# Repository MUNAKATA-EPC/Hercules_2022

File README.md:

# Hercules_2022

ヘラクレス2022シーズンのソースコード、基板データを公開しています。

詳しくはWikiを参照。

## 運用方針

- 大きな変更をするときはブランチを絶対に別途作成しましょう
- 小さな変更(スペルミスやコメント修正程度)ならどんどんmainブランチに突っ込んでもまあ構わないでしょう
- 余裕があったら変更した内容をコメントしてくれると助かります

## コードに関して

- 各プロジェクトフォルダの命名規則は「hogehoge(プロジェクト名)-teensy40(開発環境名)」となっていますが、一部試験用に作ったものに関しては、この命名規則が守られておりません...ごめんなさい。
- プロジェクトフォルダ内の「src」フォルダ内にmain.cpp(一部プロジェクトは名称が異なります)、「lib」フォルダ内に各種ライブラリ、「include」フォルダ内にサブプログラムが入っています。
- 一部PlatformIOからダウンロードしているライブラリが含まれているため、基本は「VSCode + PlatformIO」の組み合わせでご覧ください。

## 回路に関して

- 使用する設計ソフトにKiCad5と6が混在しています。
- ライブラリについてはLibraryフォルダを相対パスで参照しています。
- 発注は主にJLCPCBを使用します。

## 開発環境に関して

- VSCodeの拡張機能のPlatformIOを使用しTeensy 4.0とSeeeduino XIAOに書き込んでいます。
- 弊チームにはMacユーザーがいないため、Windows環境での開発を想定しております。Macをお使いの皆様、何か問題が生じても対応はできません。予めご了承ください。

## ライセンスに関して

- すべてのコード、基板データに関するライセンスはMITにしていますが、ライブラリ等のライセンスはそのライブラリごとのライセンスに従ってください。

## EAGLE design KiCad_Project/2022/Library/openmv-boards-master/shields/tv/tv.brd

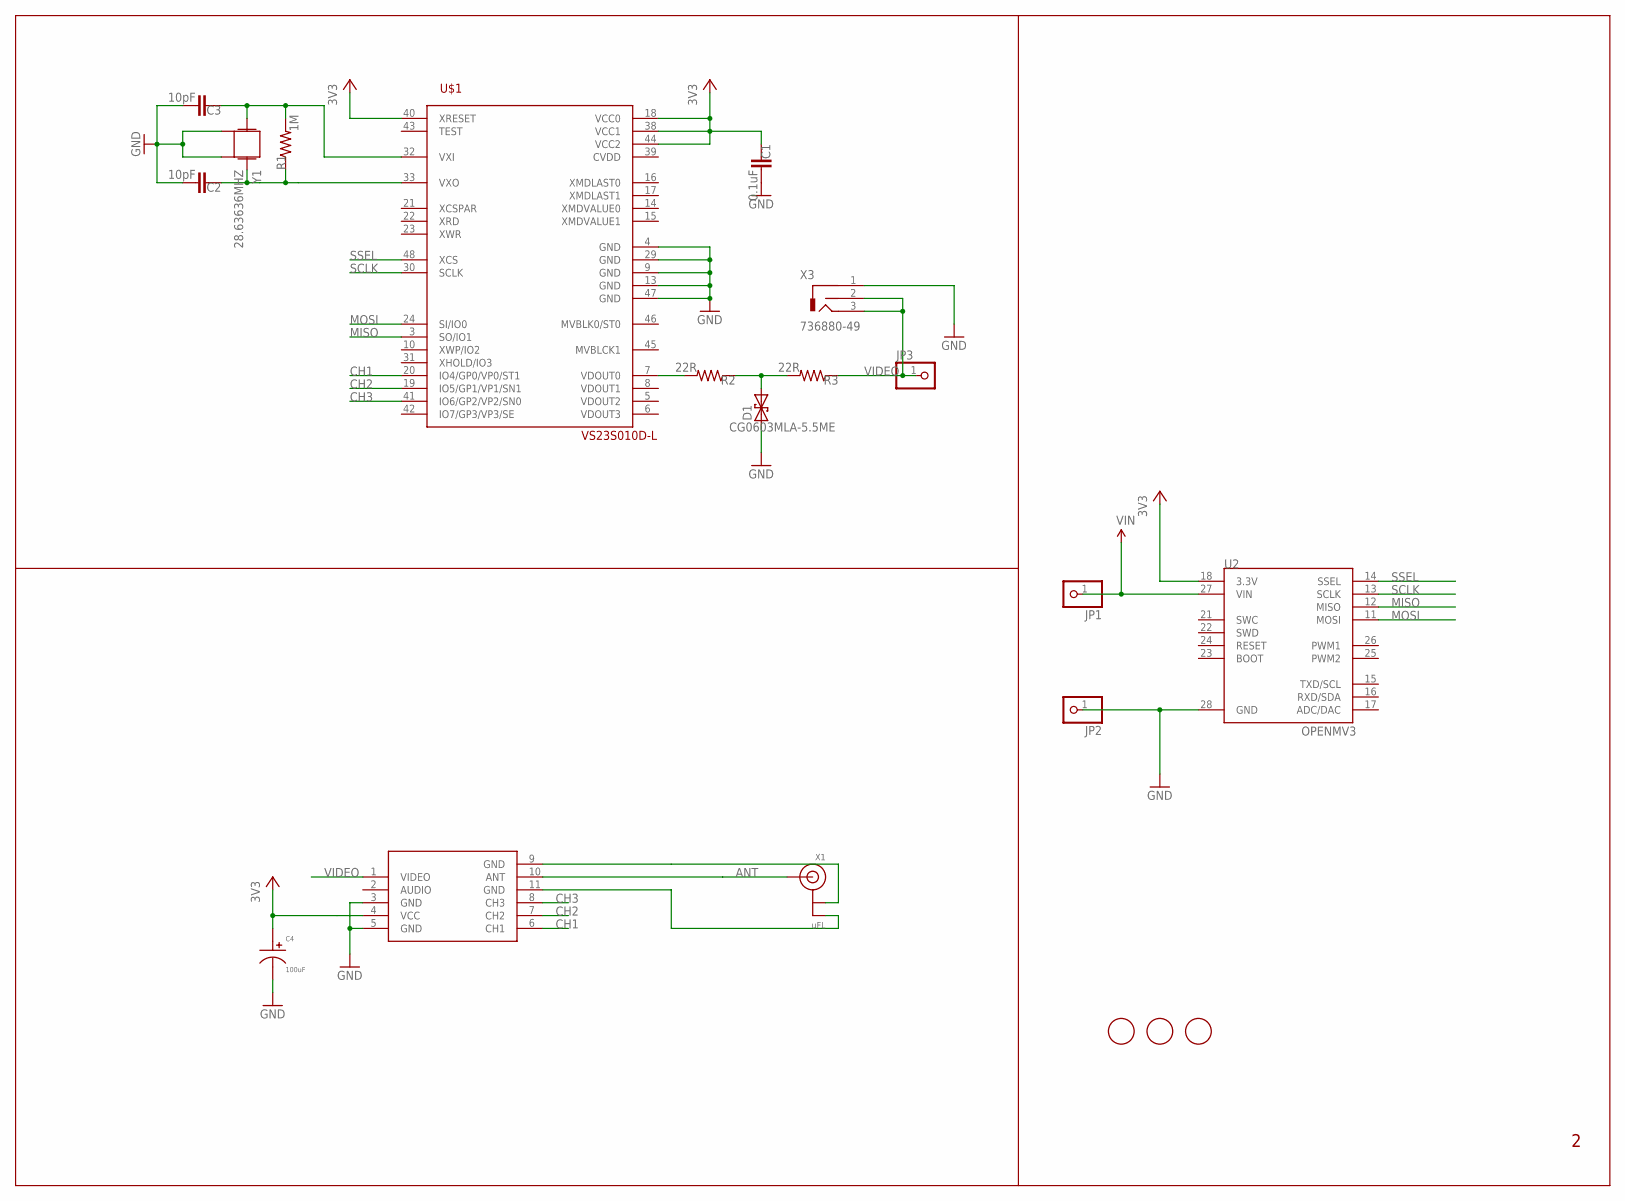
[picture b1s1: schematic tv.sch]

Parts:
C1: 0.1uF; 0603-CAP
C2, C3: 10pF; 0603-CAP
C4: 100uF; CP6.3MM
D1: CG0603MLA-5.5ME; C0603K
JP1, JP2, JP3: PINHD-1X1; 1X01
R1: 1M; 0603-RES
R2, R3: 22R; 0603-RES
U1: VS23S010D-L; LQFP48
U2: OPENMV3
U3: TX5813
U$1, U$2, U$4: FIDUCIAL; FIDUCIAL_1MM
X1: uFL; U.FL
X3: 736880-49
Y1: 28.63636MHZ; CRYSTAL-3.2X2.5-CTX851CT

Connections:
3V3: C1.1, C4.P$1, U1.18 (VCC0), U1.38 (VCC1), U1.40 (XRESET), U1.44 (VCC2), U2.18 (3.3V), U3.4 (VCC)
ANT: U3.10 (ANT), X1.3 (SIGNAL)
CH1: U1.20 (IO4/GP0/VP0/ST1), U3.6 (CH1)
CH2: U1.19 (IO5/GP1/VP1/SN1), U3.7 (CH2)
CH3: U1.41 (IO6/GP2/VP2/SN0), U3.8 (CH3)
GND: C1.2, C2.2, C3.2, C4.P$2, D1.1, JP2.1, U1.4 (GND), U1.9 (GND), U1.13 (GND), U1.29 (GND), U1.47 (GND), U2.28 (GND), U3.3 (GND), U3.5 (GND), X3.1 (GND), Y1.2, Y1.4
MISO: U1.3 (SO/IO1), U2.12 (MISO)
MOSI: U1.24 (SI/IO0), U2.11 (MOSI)
unnamed: D1.2, R2.1, R3.2
unnamed: R2.2, U1.7 (VDOUT0)
unnamed: U3.11 (GND), X1.2 (GND)
unnamed: U3.9 (GND), X1.1 (GND)
unnamed: C3.1, R1.2, U1.32 (VXI), Y1.3 (2)
unnamed: C2.1, R1.1, U1.33 (VXO), Y1.1
SCLK: U1.30 (SCLK), U2.13 (SCLK)
SSEL: U1.48 (XCS), U2.14 (SSEL)
VIDEO: JP3.1, R3.1, U3.1 (VIDEO), X3.2 (COT), X3.3 (SIGNAL)
VIN: JP1.1, U2.27 (VIN)

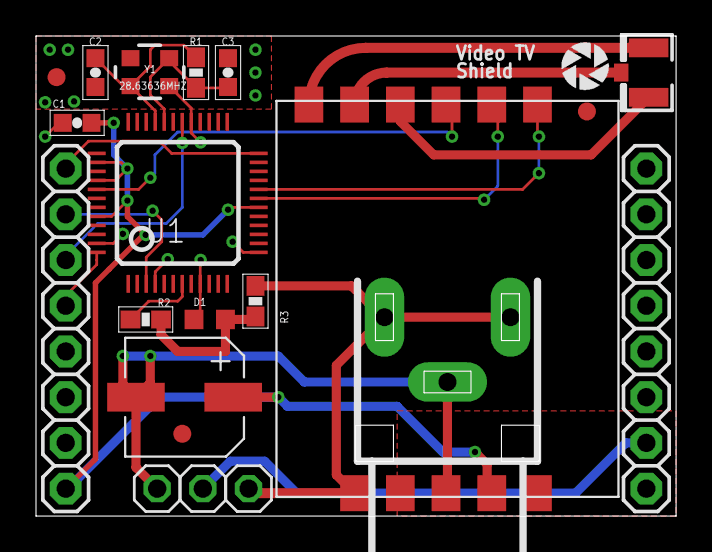
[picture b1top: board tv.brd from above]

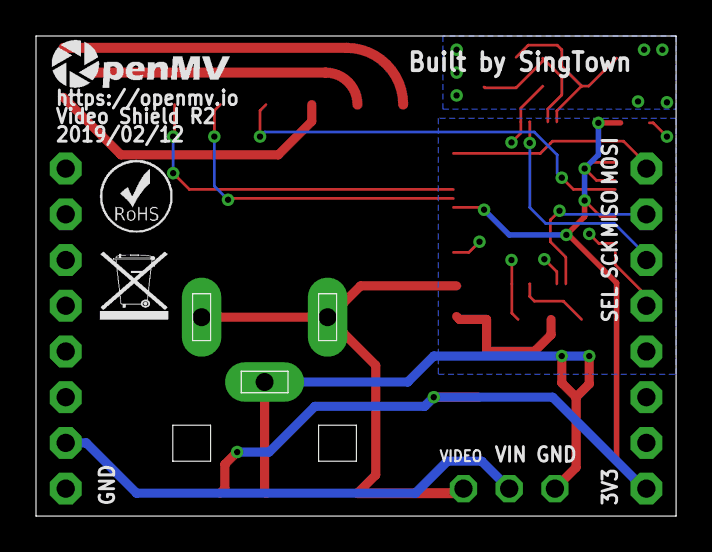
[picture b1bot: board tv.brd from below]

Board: 2 copper layers, 35.6 x 26.7 mm, 24 parts (3 on the bottom side), 18 nets.

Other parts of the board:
U$3: OMV-LOGO-SMALL
U$5: ROHS
U$6: WEEE
U$9: OPENMV-LOGO

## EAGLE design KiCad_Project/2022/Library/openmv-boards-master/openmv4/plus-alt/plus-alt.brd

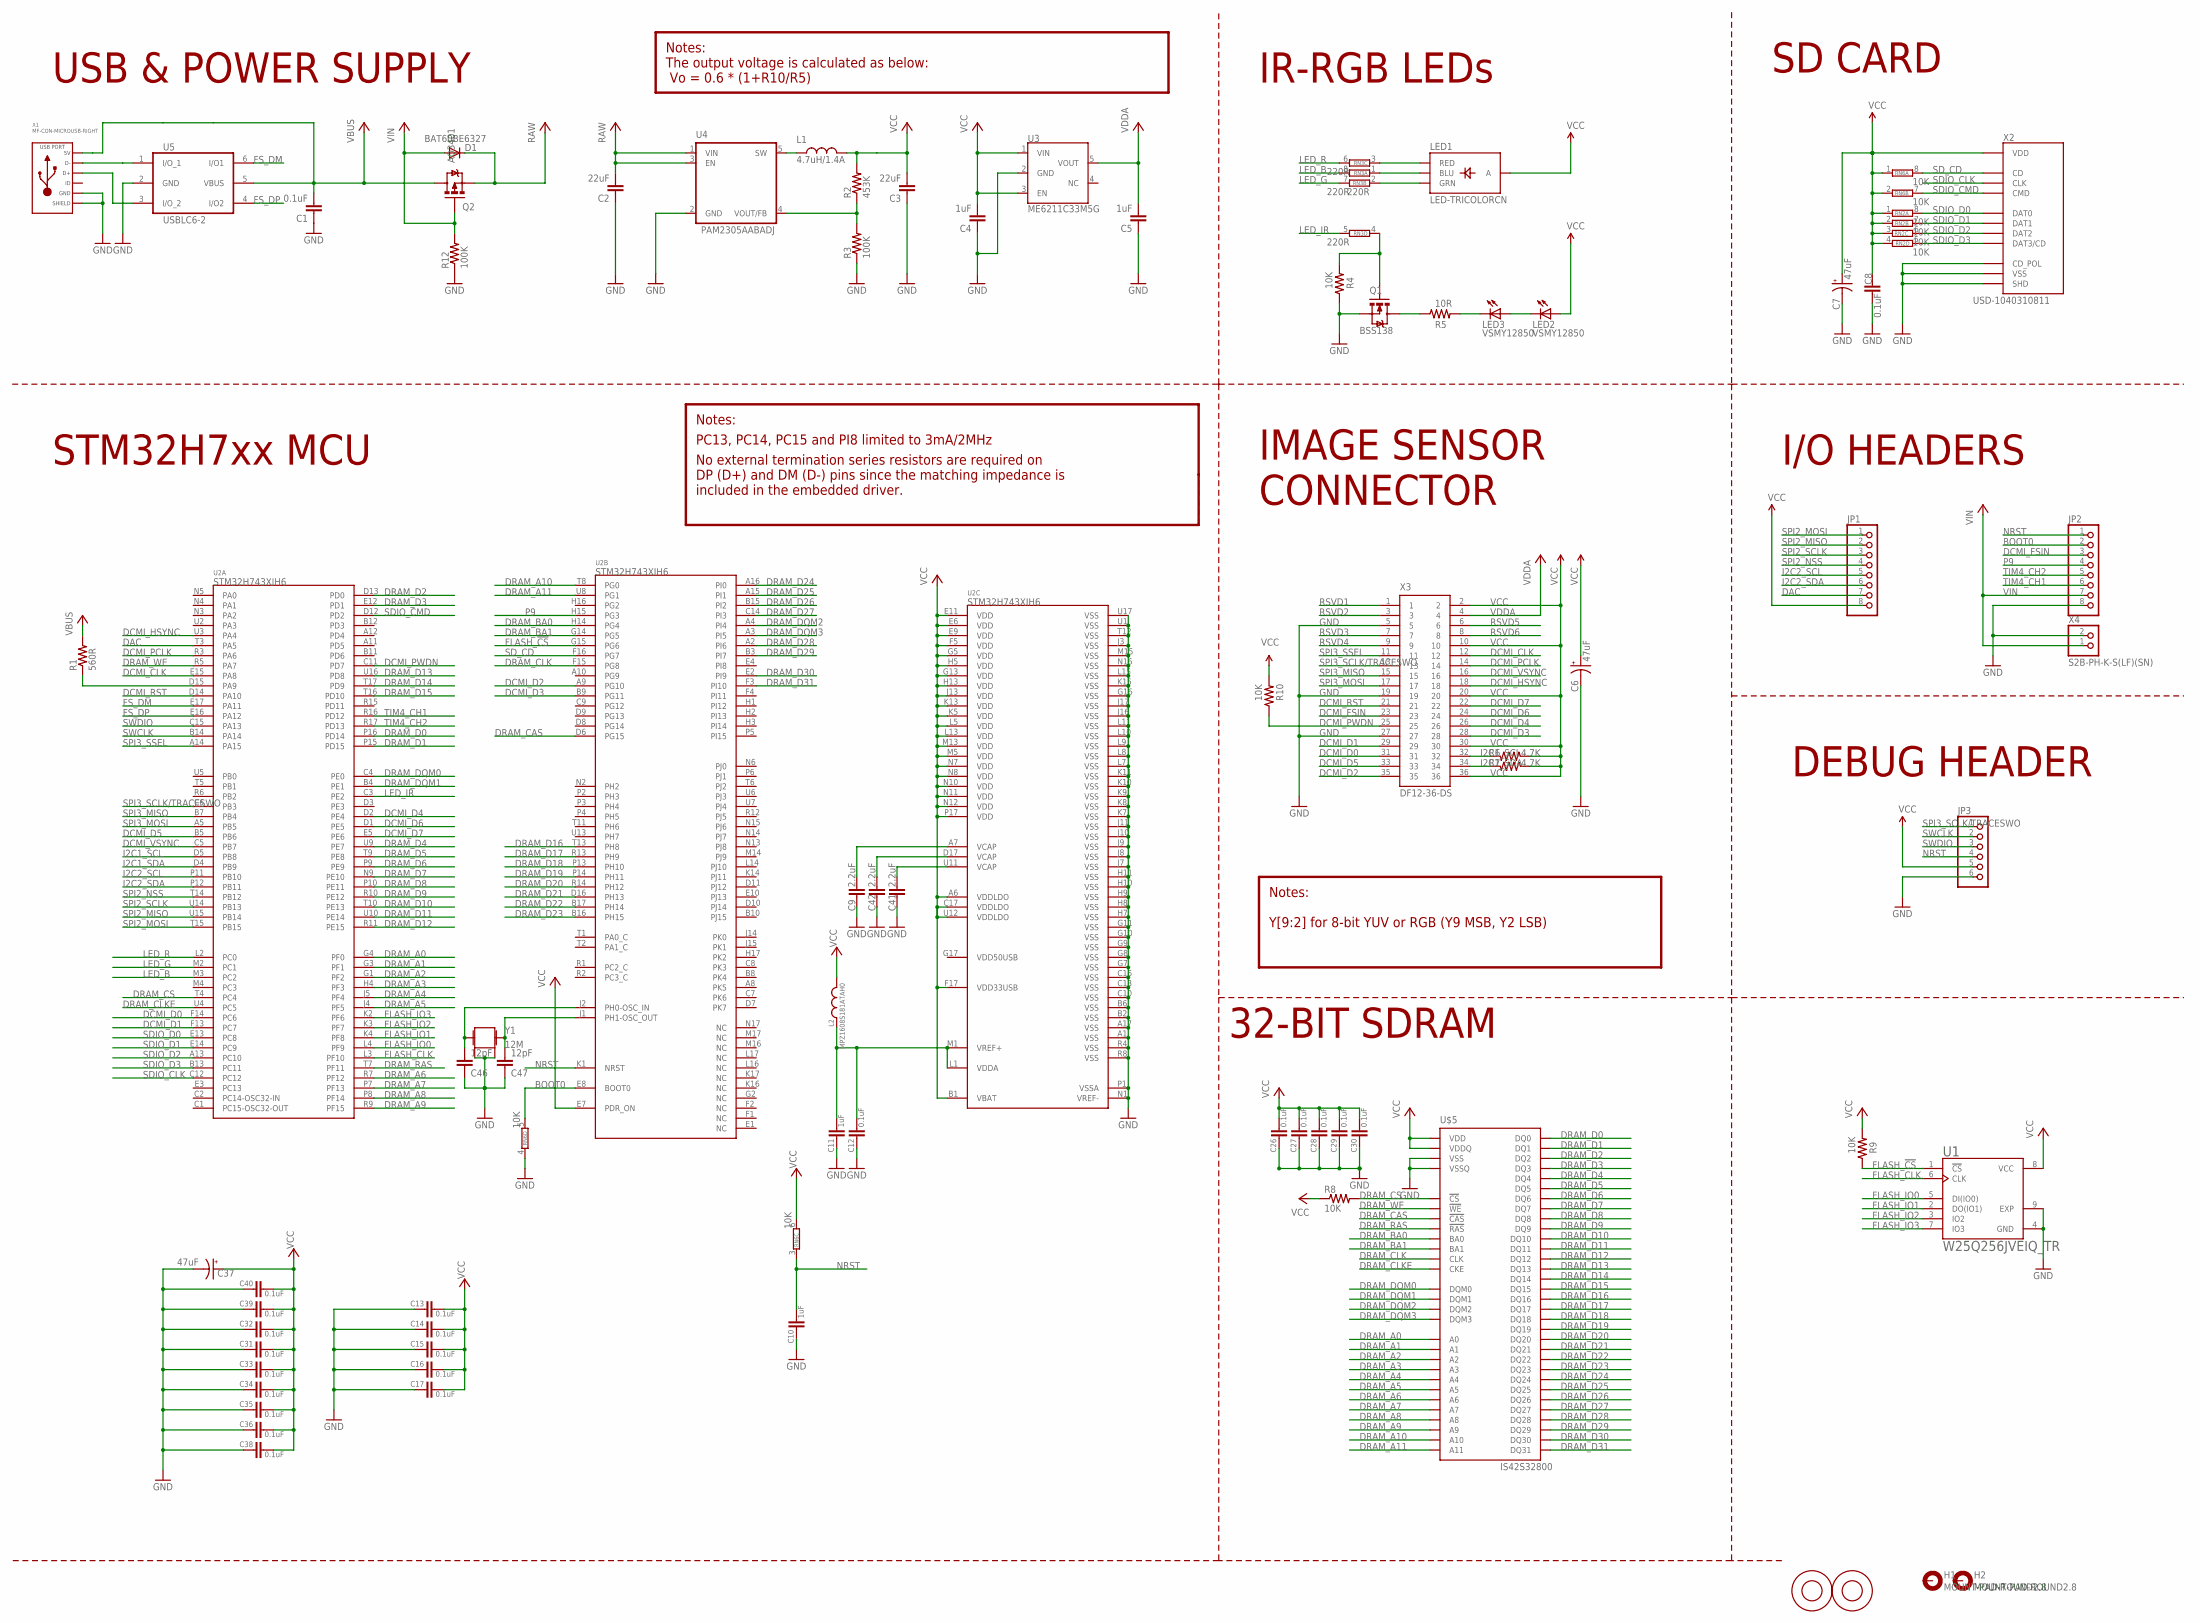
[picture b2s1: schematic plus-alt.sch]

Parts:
C1, C8, C12, C13, C14, C15, C16, C17, C26, C27, C28, C29, C30, C31, C32, C33, C34, C35, C36, C38, C39, C40: 0.1uF; 0402-CAP
C2, C3: 22uF; 0805
C4, C5, C10, C11: 1uF; 0402-CAP
C6, C7, C37: 47uF; EIA3216
C9, C41, C42: 2.2uF; 0402-CAP
C46, C47: 12pF; 0402-CAP
D1: BAT60BE6327; SOD-323
H1, H2: MOUNT-PAD-ROUND2.8; 2,8-PAD
JP1, JP2: PINHD-1X8; 1X08
JP3: PINHD-1X6; 1X06
L1: 4.7uH/1.4A; 1007
L2: MPZ1608S181ATAH0; C0402
LED1: LED-TRICOLORCN; LED-TRICOLOR-SMD
LED2, LED3: VSMY12850; LED-1206
M1, M2: 9774030243R; 9774030151R
Q1: BSS138; SOT23-3
Q2: AO3401; SOT23-3
R1: 560R; 0402-RES
R2: 453K; 0402-RES
R3, R12: 100K; 0402-RES
R4, R8, R9, R10: 10K; 0402-RES
R5: 10R; 0402-RES
R6, R7: 4.7K; 0402-RES
RN2, RN6: 10K; EXBV8V
RN3: 220R; EXBV8V
U1: W25Q256JVEIQ_TR; SON127P800X600X80-9N
U2: *; TFBGA240+25
U3: ME6211C33M5G; SOT23-5
U4: PAM2305AABADJ; TSOT25
U5: USBLC6-2; SOT-23-6L
U$5: IS42S32800; BGA90
X1: MF-CON-MICROUSB-RIGHT; MICROUSB-RIGHT
X2: USD-1040310811; 1040310811
X3: DF12-36-DS
X4: S2B-PH-K-S(LF)(SN); JST-PH-2-THM-RA
Y1: 12M; CRYSTAL-2.5X2.0

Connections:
BOOT0: JP2.2, RN6.5 (2), U2.E8 (BOOT0)
DAC: JP1.7, U2.T3 (PA5)
DCMI_CLK: U2.E15 (PA8), X3.12
DCMI_D0: U2.F14 (PC6), X3.31
DCMI_D1: U2.F13 (PC7), X3.29
DCMI_D2: U2.A9 (PG10), X3.35
DCMI_D3: U2.B9 (PG11), X3.28
DCMI_D4: U2.D2 (PE4), X3.26
DCMI_D5: U2.B5 (PB6), X3.33
DCMI_D6: U2.D1 (PE5), X3.24
DCMI_D7: U2.E5 (PE6), X3.22
DCMI_FSIN: JP2.3, X3.23
DCMI_HSYNC: U2.U3 (PA4), X3.18
DCMI_PCLK: U2.R3 (PA6), X3.14
DCMI_PWDN: R10.1, U2.C11 (PD7), X3.25
DCMI_RST: U2.D14 (PA10), X3.21
DCMI_VSYNC: U2.C5 (PB7), X3.16
DRAM_A0: U2.G4 (PF0), U$5.G8 (A0)
DRAM_A1: U2.G3 (PF1), U$5.G9 (A1)
DRAM_A2: U2.G1 (PF2), U$5.F7 (A2)
DRAM_A3: U2.H4 (PF3), U$5.F3 (A3)
DRAM_A4: U2.J5 (PF4), U$5.G1 (A4)
DRAM_A5: U2.J4 (PF5), U$5.G2 (A5)
DRAM_A6: U2.R7 (PF12), U$5.G3 (A6)
DRAM_A7: U2.P7 (PF13), U$5.H1 (A7)
DRAM_A8: U2.P8 (PF14), U$5.H2 (A8)
DRAM_A9: U2.R9 (PF15), U$5.J3 (A9)
DRAM_A10: U2.T8 (PG0), U$5.G7 (A10)
DRAM_A11: U2.U8 (PG1), U$5.H9 (A11)
DRAM_BA0: U2.H14 (PG4), U$5.J7 (BA0)
DRAM_BA1: U2.G14 (PG5), U$5.H8 (BA1)
DRAM_CAS: U2.D6 (PG15), U$5.K7 (!CAS)
DRAM_CLK: U2.F15 (PG8), U$5.J1 (CLK)
DRAM_CLKE: U2.U4 (PC5), U$5.J2 (CKE)
DRAM_CS: R8.2, U2.T4 (PC4), U$5.J8 (!CS)
DRAM_D0: U2.P16 (PD14), U$5.R8 (DQ0)
DRAM_D1: U2.P15 (PD15), U$5.N7 (DQ1)
DRAM_D2: U2.D13 (PD0), U$5.R9 (DQ2)
DRAM_D3: U2.E12 (PD1), U$5.N8 (DQ3)
DRAM_D4: U2.U9 (PE7), U$5.P9 (DQ4)
DRAM_D5: U2.T9 (PE8), U$5.M8 (DQ5)
DRAM_D6: U2.P9 (PE9), U$5.M7 (DQ6)
DRAM_D7: U2.N9 (PE10), U$5.L8 (DQ7)
DRAM_D8: U2.P10 (PE11), U$5.L2 (DQ8)
DRAM_D9: U2.R10 (PE12), U$5.M3 (DQ9)
DRAM_D10: U2.T10 (PE13), U$5.M2 (DQ10)
DRAM_D11: U2.U10 (PE14), U$5.P1 (DQ11)
DRAM_D12: U2.R11 (PE15), U$5.N2 (DQ12)
DRAM_D13: U2.U16 (PD8), U$5.R1 (DQ13)
DRAM_D14: U2.T17 (PD9), U$5.N3 (DQ14)
DRAM_D15: U2.T16 (PD10), U$5.R2 (DQ15)
DRAM_D16: U2.T13 (PH8), U$5.E8 (DQ16)
DRAM_D17: U2.R13 (PH9), U$5.D7 (DQ17)
DRAM_D18: U2.P13 (PH10), U$5.D8 (DQ18)
DRAM_D19: U2.P14 (PH11), U$5.B9 (DQ19)
DRAM_D20: U2.R14 (PH12), U$5.C8 (DQ20)
DRAM_D21: U2.D16 (PH13), U$5.A9 (DQ21)
DRAM_D22: U2.B17 (PH14), U$5.C7 (DQ22)
DRAM_D23: U2.B16 (PH15), U$5.A8 (DQ23)
DRAM_D24: U2.A16 (PI0), U$5.A2 (DQ24)
DRAM_D25: U2.A15 (PI1), U$5.C3 (DQ25)
DRAM_D26: U2.B15 (PI2), U$5.A1 (DQ26)
DRAM_D27: U2.C14 (PI3), U$5.C2 (DQ27)
DRAM_D28: U2.A2 (PI6), U$5.B1 (DQ28)
DRAM_D29: U2.B3 (PI7), U$5.D2 (DQ29)
DRAM_D30: U2.E2 (PI9), U$5.D3 (DQ30)
DRAM_D31: U2.F3 (PI10), U$5.E2 (DQ31)
DRAM_DQM0: U2.C4 (PE0), U$5.K9 (DQM0)
DRAM_DQM1: U2.B4 (PE1), U$5.K1 (DQM1)
DRAM_DQM2: U2.A4 (PI4), U$5.F8 (DQM2)
DRAM_DQM3: U2.A3 (PI5), U$5.F2 (DQM3)
DRAM_RAS: U2.T7 (PF11), U$5.J9 (!RAS)
DRAM_WE: U2.R5 (PA7), U$5.K8 (!WE)
FLASH_!CS: R9.1, U1.1 (!CS), U2.G15 (PG6)
FLASH_CLK: U1.6 (CLK), U2.L3 (PF10)
FLASH_IO0: U1.5 (DI(IO0)), U2.L4 (PF9)
FLASH_IO1: U1.2 (DO(IO1)), U2.K4 (PF8)
FLASH_IO2: U1.3 (IO2), U2.K3 (PF7)
FLASH_IO3: U1.7 (IO3), U2.K2 (PF6)
FS_DM: U2.E17 (PA11), U5.6 (I/O1)
FS_DP: U2.E16 (PA12), U5.4 (I/O2)
GND: C1.1, C2.1, C3.1, C4.1, C5.1, C6.C (-), C7.C (-), C8.2, C9.2, C10.2, C11.2, C12.2, C13.2, C14.2, C15.2, C16.2, C17.2, C26.2, C27.2, C28.2, C29.2, C30.2, C31.2, C32.2, C33.2, C34.2, C35.2, C36.2, C37.C (-), C38.2, C39.2, C40.2, C41.2, C42.2, C46.1, C47.1, JP2.8, JP3.6, Q1.2 (S), R3.1, R4.1, R12.1, RN6.4 (1), U1.4 (GND), U1.9 (EXP), U2.A1 (VSS), U2.A17 (VSS), U2.B2 (VSS), U2.B6 (VSS), U2.C10 (VSS), U2.C13 (VSS), U2.C16 (VSS), U2.G7 (VSS), U2.G8 (VSS), U2.G9 (VSS), U2.G10 (VSS), U2.G11 (VSS), U2.G16 (VSS), U2.H7 (VSS), U2.H8 (VSS), U2.H9 (VSS), U2.H10 (VSS), U2.H11 (VSS), U2.J3 (VSS), U2.J7 (VSS), U2.J8 (VSS), U2.J9 (VSS), U2.J10 (VSS), U2.J11 (VSS), U2.J16 (VSS), U2.J17 (VSS), U2.K7 (VSS), U2.K8 (VSS), U2.K9 (VSS), U2.K10 (VSS), U2.K11 (VSS), U2.K15 (VSS), U2.L7 (VSS), U2.L8 (VSS), U2.L9 (VSS), U2.L10 (VSS), U2.L11 (VSS), U2.L15 (VSS), U2.M15 (VSS), U2.N1 (VREF-), U2.N16 (VSS), U2.P1 (VSSA), U2.R4 (VSS)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
I2C1_SCL: R6.2, U2.D5 (PB8), X3.32
I2C1_SDA: R7.2, U2.D4 (PB9), X3.34
I2C2_SCL: JP1.5, U2.P11 (PB10)
I2C2_SDA: JP1.6, U2.P12 (PB11)
LED_B: RN3.8 (2), U2.M3 (PC2)
LED_G: RN3.7 (2), U2.M2 (PC1)
LED_IR: RN3.5 (2), U2.C3 (PE2)
LED_R: RN3.6 (2), U2.L2 (PC0)
unnamed: U5.1 (I/O_1), X1.2 (D-)
unnamed: U5.3 (I/O_2), X1.3 (D+)
unnamed: Q1.1 (G), R4.2, RN3.4 (1)
unnamed: LED1.B (BLU), RN3.1
unnamed: LED1.R (RED), RN3.3 (1)
unnamed: LED1.G (GRN), RN3.2 (1)
unnamed: LED3.C, R5.2
unnamed: R2.1, R3.2, U4.4 (VOUT/FB)
unnamed: Q1.3 (D), R5.1
unnamed: LED2.C, LED3.A
unnamed: C11.1, C12.1, L2.1, U2.L1 (VDDA), U2.M1 (VREF+)
unnamed: R1.1, U2.D15 (PA9)
unnamed: C46.2, U2.J2 (PH0-OSC_IN), Y1.3 (2)
unnamed: C47.2, U2.J1 (PH1-OSC_OUT), Y1.1
NRST: C10.1, JP2.1, JP3.4, RN6.3 (1), U2.K1 (NRST)
P9: JP2.4, U2.H15 (PG3)
RAW: C2.2, D1.1 (C), Q2.2 (S), U4.1 (VIN), U4.3 (EN)
RSVD1: X3.1
RSVD2: X3.3
RSVD3: X3.7
RSVD4: X3.9
RSVD5: X3.6
RSVD6: X3.8
SDIO_CLK: U2.C12, X2.P$5 (CLK)
SDIO_CMD: RN6.7 (2), U2.D12 (PD2), X2.P$3 (CMD)
SDIO_D0: RN2.8 (2), U2.E13 (PC8), X2.P$7 (DAT0)
SDIO_D1: RN2.7 (2), U2.E14 (PC9), X2.P$8 (DAT1)
SDIO_D2: RN2.6 (2), U2.A13 (PC10), X2.P$1 (DAT2)
SDIO_D3: RN2.5 (2), U2.B13 (PC11), X2.P$2 (DAT3/CD)
SD_CD: RN6.8 (2), U2.F16 (PG7), X2.CD$1 (CD)
SPI2_MISO: JP1.2, U2.U15 (PB14)
SPI2_MOSI: JP1.1, U2.T15 (PB15)
SPI2_NSS: JP1.4, U2.T14 (PB12)
SPI2_SCLK: JP1.3, U2.U14 (PB13)
SPI3_MISO: U2.B7 (PB4), X3.15
SPI3_MOSI: U2.A5 (PB5), X3.17
SPI3_SCLK/TRACESWO: JP3.1, U2.C6 (PB3), X3.13
SPI3_SSEL: U2.A14 (PA15), X3.11
SW: L1.1, U4.5 (SW)
SWCLK: JP3.2, U2.B14 (PA14)
SWDIO: JP3.3, U2.C15 (PA13)
TIM4_CH1: JP2.6, U2.R16 (PD12)
TIM4_CH2: JP2.5, U2.R17 (PD13)
VBUS: C1.2, Q2.3 (D), R1.2, U5.5 (VBUS), X1.1 (5V)
VCAP1: C9.1, U2.A7 (VCAP)
VCAP3: C41.1, U2.U11 (VCAP)
VCAP4: C42.1, U2.D17 (VCAP)
VCC: C3.2, C4.2, C6.A (+), C7.A (+), C8.1, C13.1, C14.1, C15.1, C16.1, C17.1, C26.1, C27.1, C28.1, C29.1, C30.1, C31.1, C32.1, C33.1, C34.1, C35.1, C36.1, C37.A (+), C38.1, C39.1, C40.1, JP1.8, JP3.5, L1.2, L2.2, LED1.V (A), LED2.A, R2.2, R6.1, R7.1, R8.1, R9.2, R10.2, RN2.1, RN2.2 (1), RN2.3 (1), RN2.4 (1), RN6.1, RN6.2 (1), RN6.6 (2), U1.8 (VCC), U2.A6 (VDDLDO), U2.B1 (VBAT), U2.C17 (VDDLDO), U2.E6 (VDD), U2.E7 (PDR_ON), U2.E9 (VDD), U2.E11 (VDD), U2.F5 (VDD), U2.F17 (VDD33USB), U2.G5 (VDD), U2.G13 (VDD), U2.H5 (VDD), U2.H13 (VDD), U2.J13 (VDD), U2.K5 (VDD), U2.K13 (VDD), U2.L5 (VDD), U2.L13 (VDD), U2.M5 (VDD), U2.M13 (VDD), U2.N7 (VDD), U2.N8 (VDD), U2.N10 (VDD), U2.N11 (VDD), U2.N12 (VDD), U2.P17 (VDD), U2.U12 (VDDLDO), U3.1 (VIN), U3.3 (EN), U$5.A7 (VDD), U$5.B2 (VDDQ), U$5.B7 (VDDQ), U$5.C9 (VDDQ), U$5.D9 (VDDQ), U$5.E1 (VDDQ), U$5.F9 (VDD), U$5.L1 (VDDQ), U$5.L7 (VDD), U$5.M9 (VDDQ), U$5.N9 (VDDQ), U$5.P2 (VDDQ), U$5.P7 (VDDQ), U$5.R7 (VDD)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
VDDA: C5.2, U3.5 (VOUT), X3.4
VIN: D1.2 (A), JP2.7, Q2.1 (G), R12.2, X4.1 (2)

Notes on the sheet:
PC13, PC14, PC15 and PI8 limited to 3mA/2MHz
SD CARD
Y[9:2] for 8-bit YUV or RGB (Y9 MSB, Y2 LSB)
Notes:
IMAGE SENSOR CONNECTOR
STM32H7xx MCU
IR-RGB LEDs
USB & POWER SUPPLY
DEBUG HEADER
I/O HEADERS
No external termination series resistors are required on DP (D+) and DM (D-) pins since the matching impedance is included in the embedded driver.
The output voltage is calculated as below: Vo = 0.6 * (1+R10/R5)
32-BIT SDRAM

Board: 6 copper layers, 80 parts (25 on the bottom side), 134 nets, no tracks yet.

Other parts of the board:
U$1: WEEE
U$2: ROHS
U$3: OMV-LOGO
U$4: OMV-LOGO-SMALL

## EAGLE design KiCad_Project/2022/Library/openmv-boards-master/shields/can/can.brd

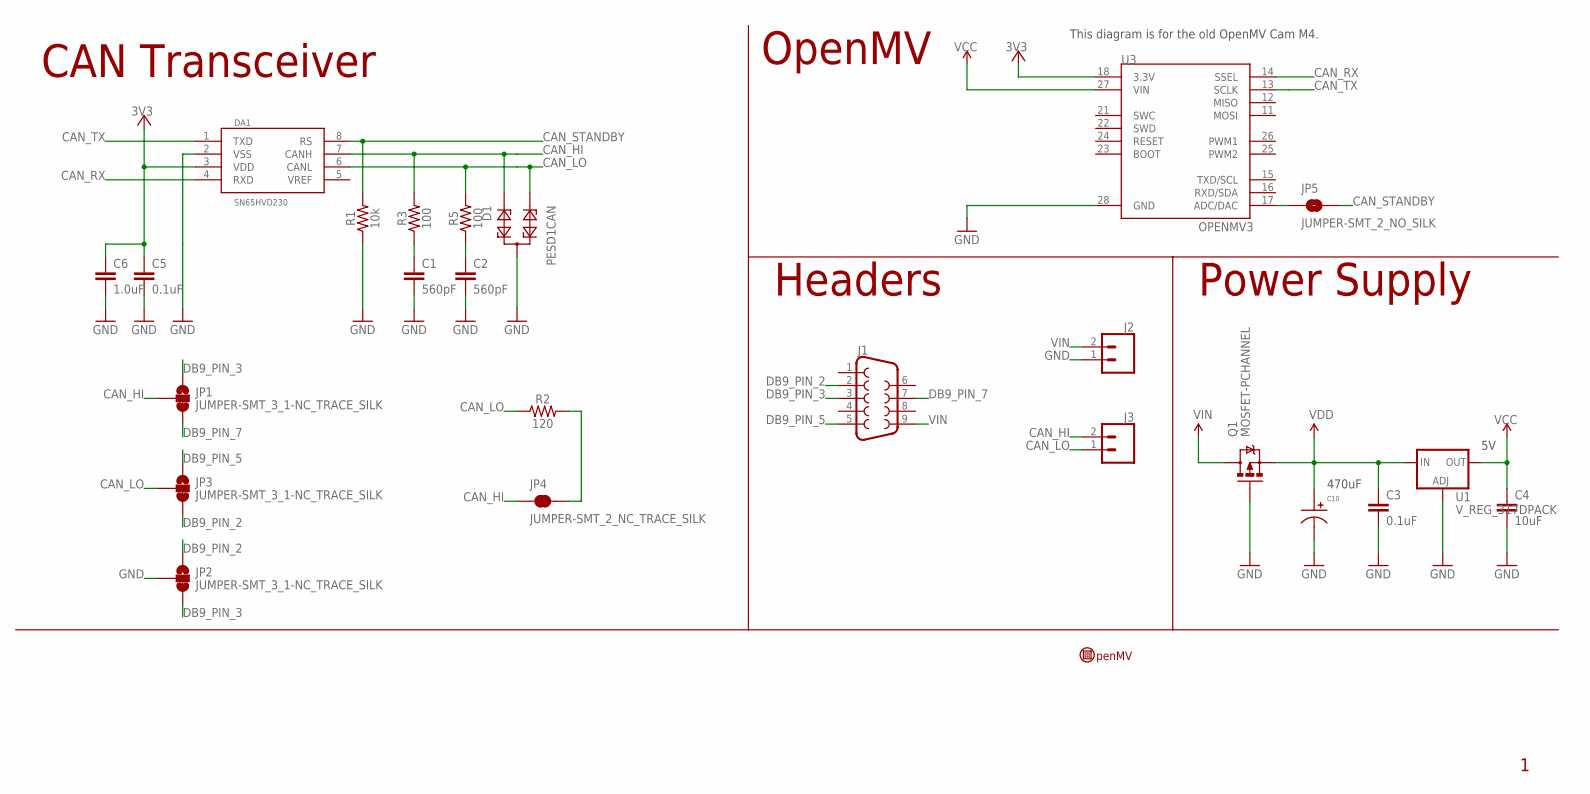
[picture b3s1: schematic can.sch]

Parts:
C1, C2: 560pF; 0603
C3: 0.1uF; 0603-CAP
C4: 10uF; 0805
C5: 0.1uF; 0603
C6: 1.0uF; 0603
C10: CAPACITOR_P_10MM; CP10MM
D1: PESD1CAN; SOT23
DA1: SN65HVD230; SO08
J1: DB9MALE; DB9_MALE
J2, J3: CONN_02; 1X02
JP1, JP2, JP3: JUMPER-SMT_3_1-NC_TRACE_SILK; SMT-JUMPER_3_1-NC_TRACE_SILK
JP4: JUMPER-SMT_2_NC_TRACE_SILK; SMT-JUMPER_2_NC_TRACE_SILK
JP5: JUMPER-SMT_2_NO_SILK; SMT-JUMPER_2_NO_SILK
Q1: MOSFET-PCHANNEL; SOT23-3
R1: 10k; 0603
R2: 120; 0603
R3, R5: 100; 0603
U1: V_REG_317DPACK; V-REG_DPACK
U3: OPENMV3
U$9: OPENMV-LOGO

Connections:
3V3: C5.1, C6.1, DA1.3 (VDD), U3.18 (3.3V)
CAN_HI: D1.1, DA1.7 (CANH), J3.2, JP1.2, JP4.1, R3.2
CAN_HI_BALANCE: C1.1, R3.1
CAN_LO: D1.2, DA1.6 (CANL), J3.1, JP3.2, R2.1, R5.2
CAN_LO_BALANCE: C2.1, R5.1
CAN_RX: DA1.4 (RXD), U3.14 (SSEL)
CAN_STANDBY: DA1.8 (RS), JP5.2, R1.2
CAN_TX: DA1.1 (TXD), U3.13 (SCLK)
DB9_PIN_2: J1.2, JP2.1, JP3.3
DB9_PIN_3: J1.3, JP1.1, JP2.3
DB9_PIN_5: J1.5, JP3.1
DB9_PIN_7: J1.7, JP1.3
GND: C1.2, C2.2, C3.2, C4.2, C5.2, C6.2, C10.P$2, D1.3, DA1.2 (VSS), J2.1, JP2.2, Q1.1 (G), R1.1, U1.1 (ADJ), U3.28 (GND)
OPENMV_STANDBY: JP5.1, U3.17 (ADC/DAC)
TERM: JP4.2, R2.2
VCC: C4.1, U1.4 (OUT), U3.27 (VIN)
VDD: C3.1, C10.P$1, Q1.2 (S), U1.3 (IN)
VIN: J1.9, J2.2, Q1.3 (D)

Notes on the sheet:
Headers
OpenMV
Power Supply
This diagram is for the old OpenMV Cam M4.
470uF
CAN Transceiver

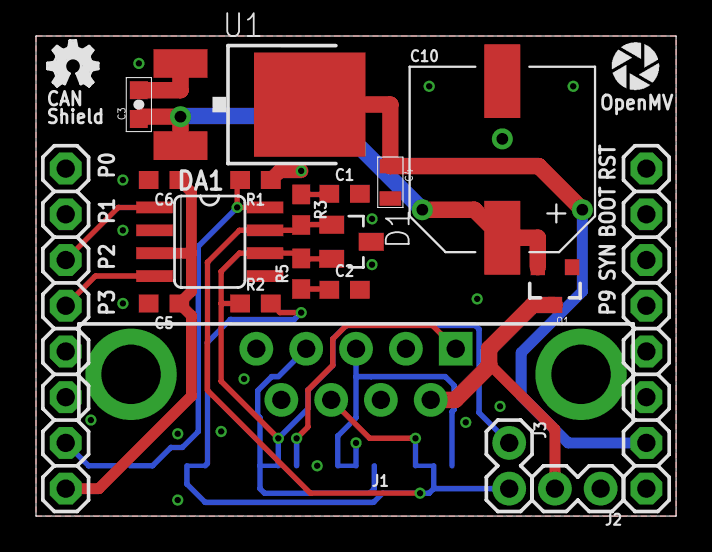
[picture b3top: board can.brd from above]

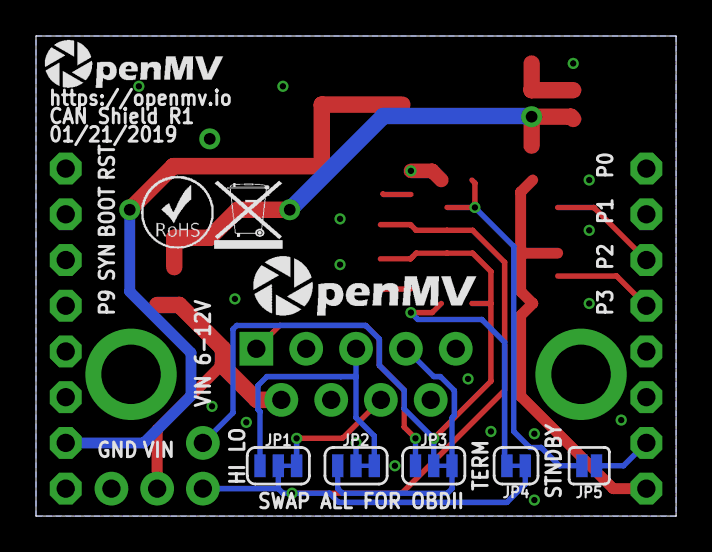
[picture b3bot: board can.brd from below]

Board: 2 copper layers, 35.6 x 26.7 mm, 30 parts (9 on the bottom side), 18 nets.

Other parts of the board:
U$3: OMV-LOGO
U$5: ROHS
U$6: WEEE
U$10: OMV-LOGO-SMALL
U$11: OSHW_FILLX100_NOTEXT

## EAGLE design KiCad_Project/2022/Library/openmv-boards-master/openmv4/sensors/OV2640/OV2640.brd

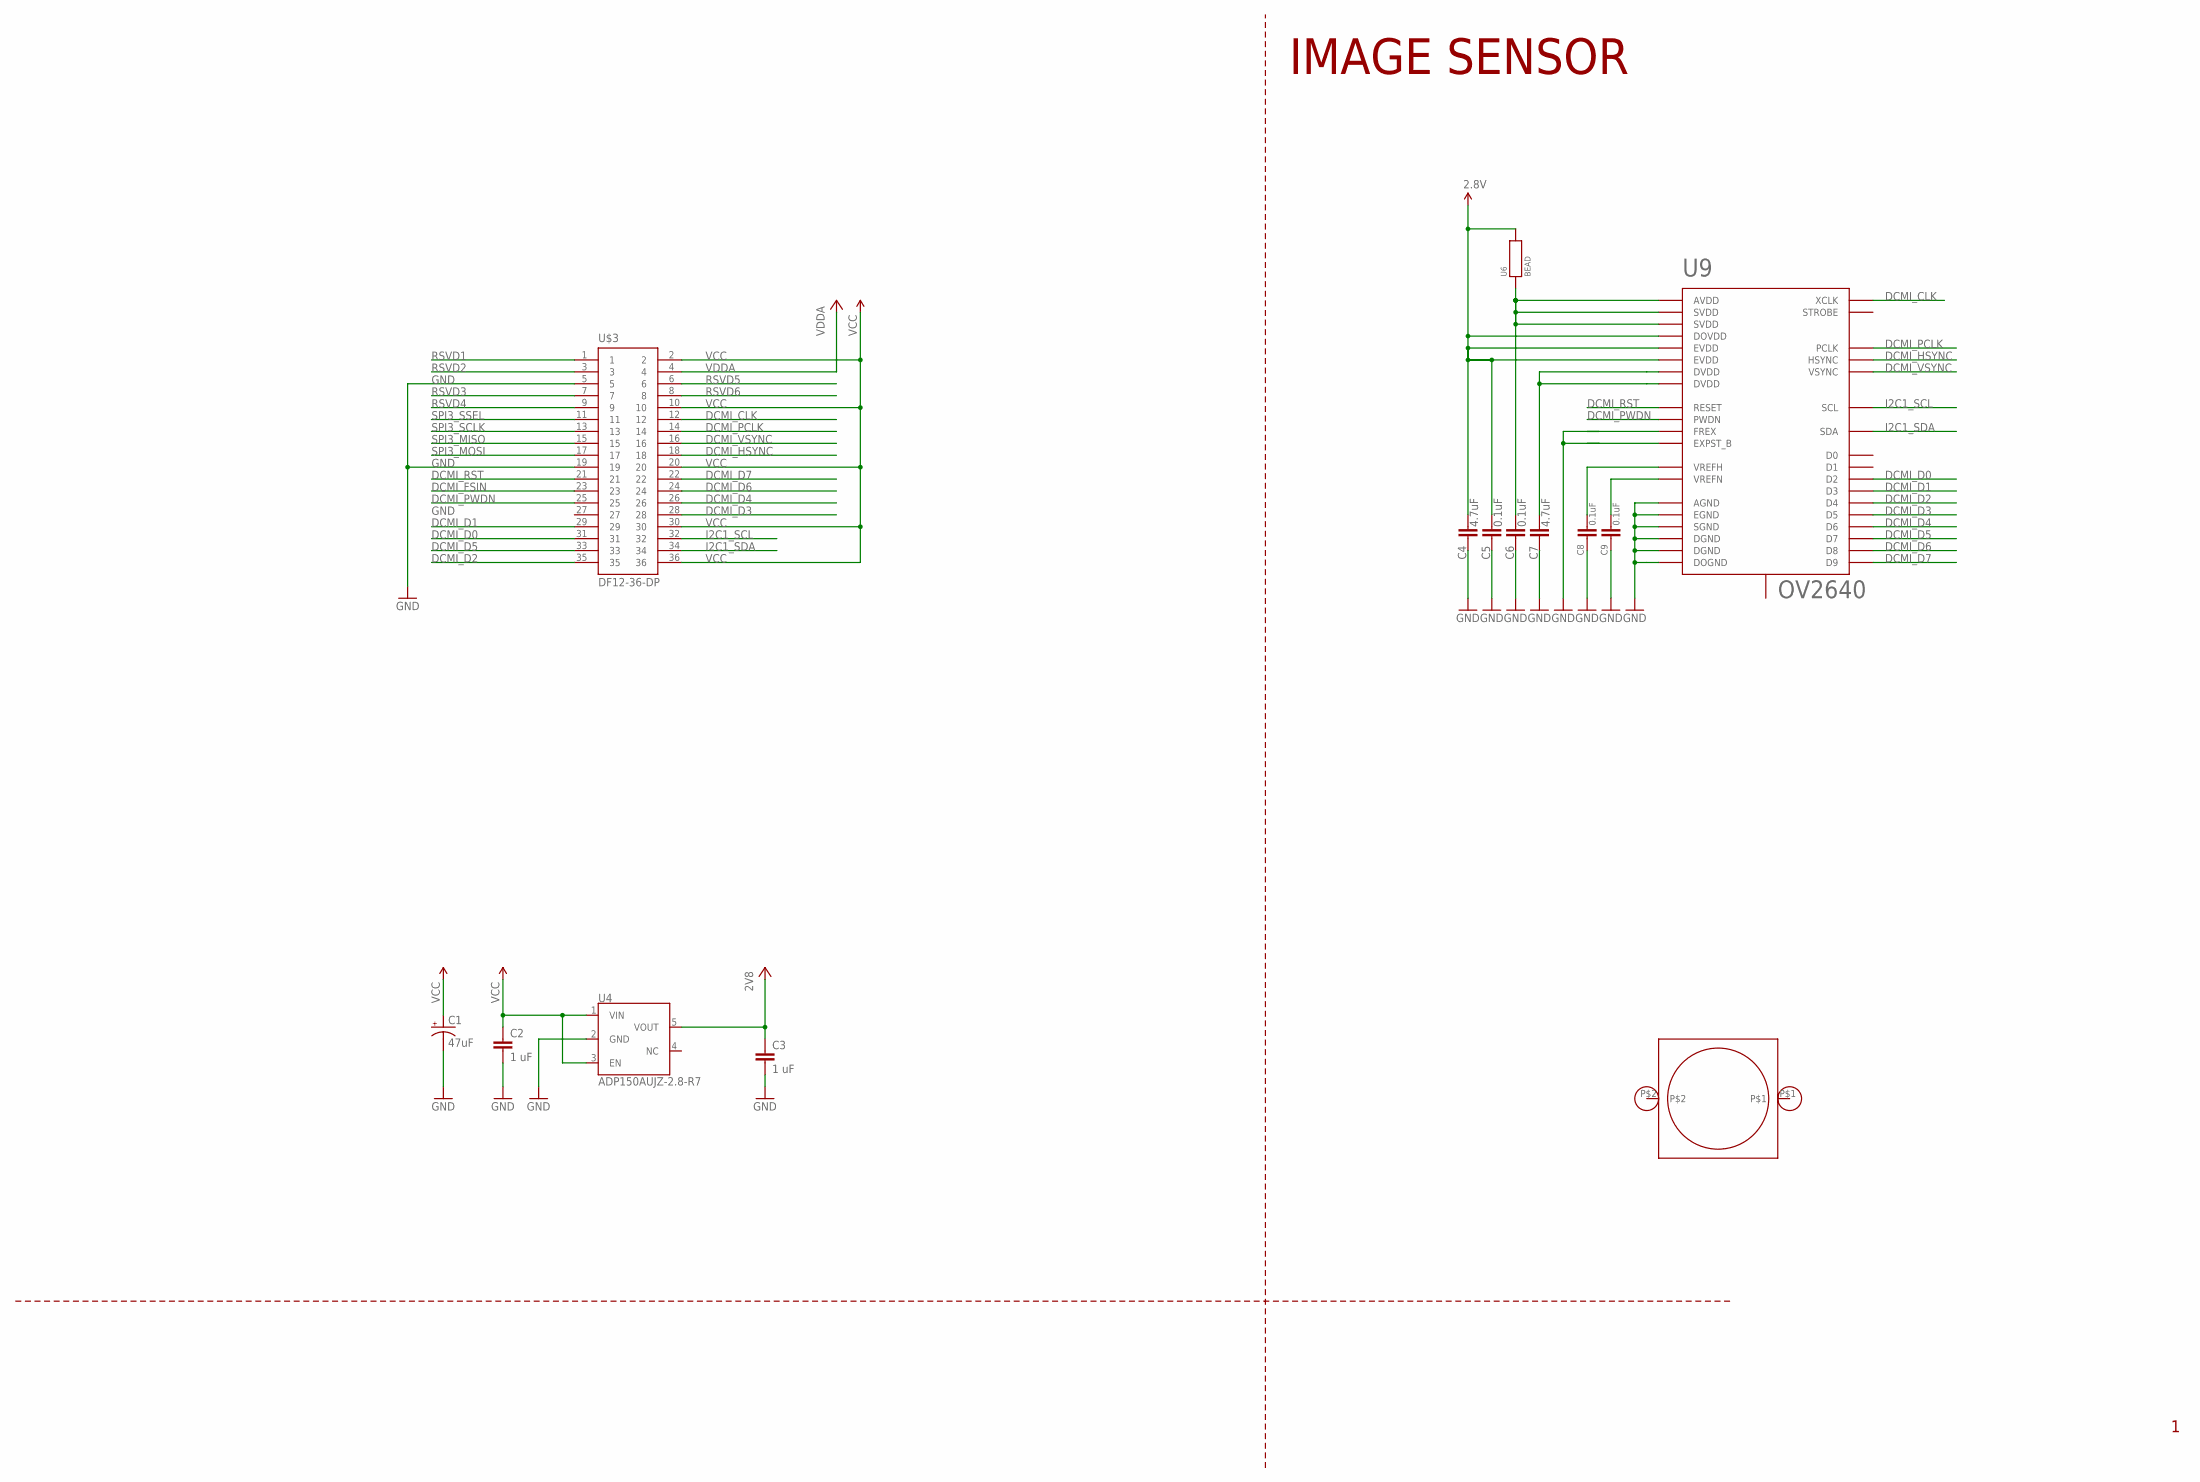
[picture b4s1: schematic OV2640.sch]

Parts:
C1: 47uF; EIA3216
C2, C3: 1 uF; 0402-CAP
C4, C7: 4.7uF; 0402-CAP
C5, C6, C8, C9: 0.1uF; 0402-CAP
LM1: LENSMOUNT20MM; LENSMOUNT-20MM
U4: ADP150AUJZ-2.8-R7; SOT23-5
U6: BEAD; 0402-CAP
U9: OV2640; CSP2
U$3: DF12-36-DP

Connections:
2.8V: C4.1, C5.1, U6.2, U9.B1 (DOVDD), U9.F1 (EVDD), U9.G1 (EVDD)
2V8: C3.1, U4.5 (VOUT)
DCMI_CLK: U9.C4 (XCLK), U$3.12
DCMI_D0: U9.F3 (D2), U$3.31
DCMI_D1: U9.G3 (D3), U$3.29
DCMI_D2: U9.F4 (D4), U$3.35
DCMI_D3: U9.G4 (D5), U$3.28
DCMI_D4: U9.E5 (D6), U$3.26
DCMI_D5: U9.G5 (D7), U$3.33
DCMI_D6: U9.F5 (D8), U$3.24
DCMI_D7: U9.G6 (D9), U$3.22
DCMI_FSIN: U$3.23
DCMI_HSYNC: U9.C3 (HSYNC), U$3.18
DCMI_PCLK: U9.E3 (PCLK), U$3.14
DCMI_PWDN: U9.B6 (PWDN), U$3.25
DCMI_RST: U9.C6 (RESET), U$3.21
DCMI_VSYNC: U9.D2 (VSYNC), U$3.16
GND: C1.C (-), C2.2, C3.2, C4.2, C5.2, C6.2, C7.2, C8.2, C9.2, U4.2 (GND), U9.A1 (DOGND), U9.A2 (EXPST_B), U9.A3 (AGND), U9.A4 (SGND), U9.B2 (FREX), U9.E4 (EGND), U9.E6 (DGND), U9.G2 (DGND), U$3.5, U$3.19
I2C1_SCL: U9.C2 (SCL), U$3.32
I2C1_SDA: U9.C1 (SDA), U$3.34
unnamed: C8.1, U9.C5 (VREFH)
unnamed: C9.1, U9.A5 (VREFN)
unnamed: C7.1, U9.F2 (DVDD), U9.F6 (DVDD)
unnamed: C6.1, U6.1, U9.B3 (AVDD), U9.B4 (SVDD), U9.B5 (SVDD)
RSVD1: U$3.1
RSVD2: U$3.3
RSVD3: U$3.7
RSVD4: U$3.9
RSVD5: U$3.6
RSVD6: U$3.8
SPI3_MISO: U$3.15
SPI3_MOSI: U$3.17
SPI3_SCLK: U$3.13
SPI3_SSEL: U$3.11
VCC: C1.A (+), C2.1, U4.1 (VIN), U4.3 (EN), U$3.2, U$3.10, U$3.20, U$3.30, U$3.36
VDDA: U$3.4

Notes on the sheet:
IMAGE SENSOR

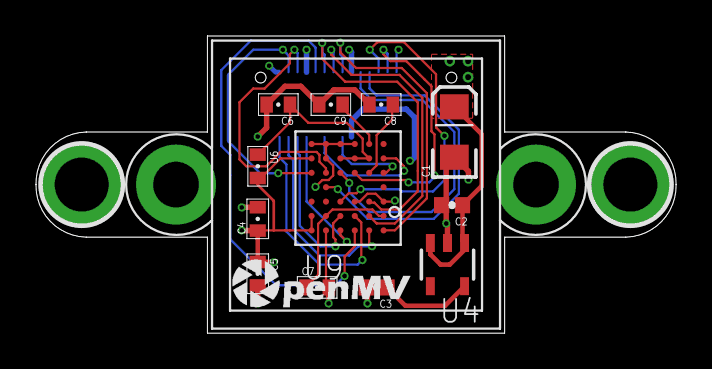
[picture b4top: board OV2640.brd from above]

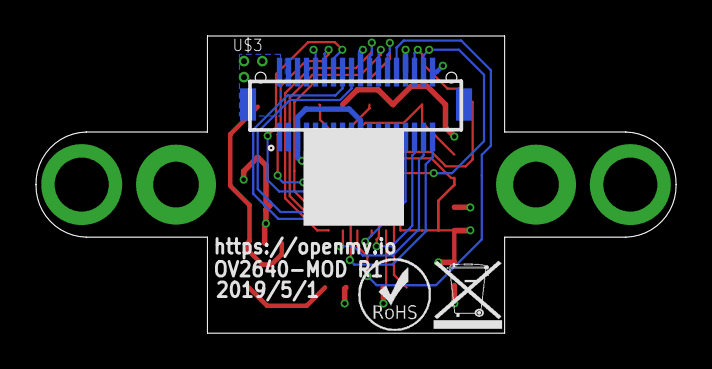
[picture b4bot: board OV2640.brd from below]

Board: 4 copper layers, 35.6 x 16.5 mm, 17 parts (3 on the bottom side), 24 nets.

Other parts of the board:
U$1: WEEE
U$2: ROHS
U$4: OMV-LOGO-SMALL

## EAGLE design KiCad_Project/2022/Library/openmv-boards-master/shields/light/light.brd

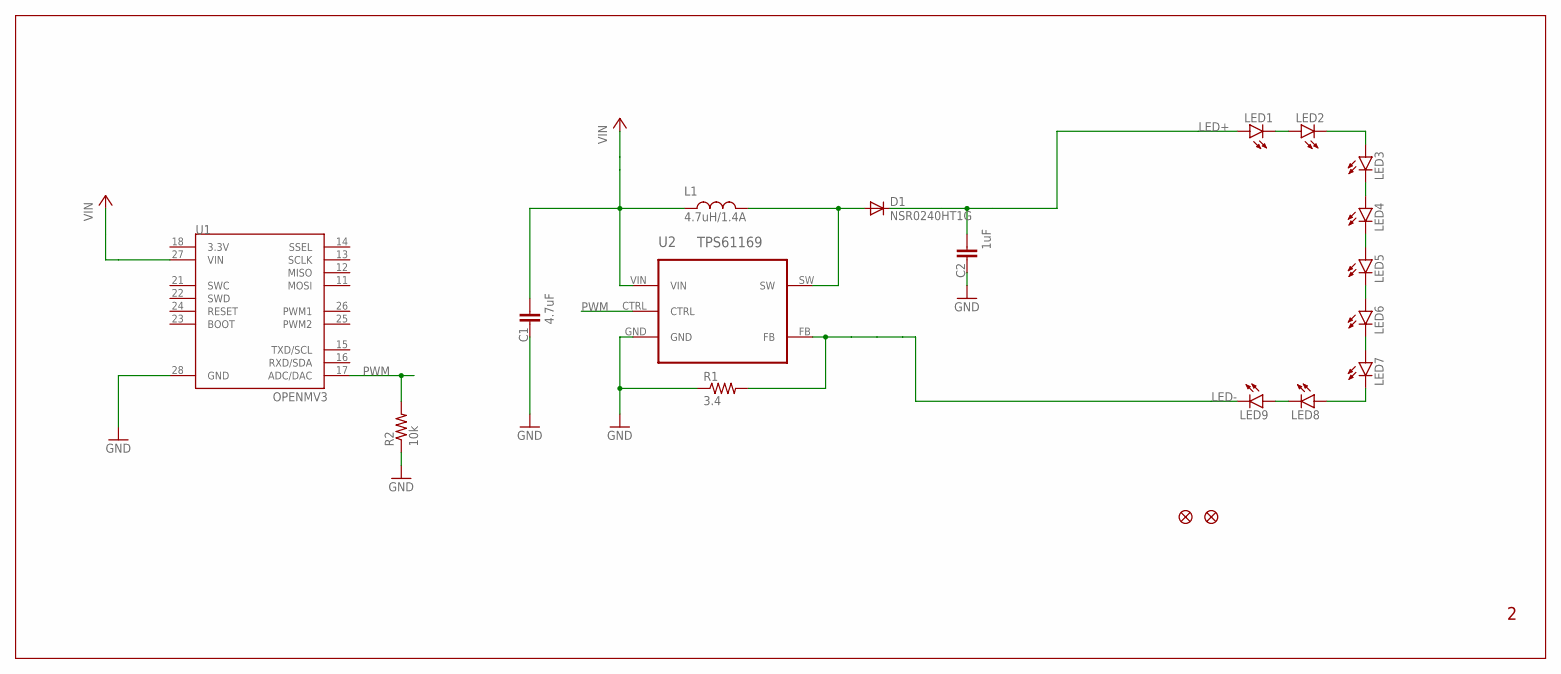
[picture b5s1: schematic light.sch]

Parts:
C1: 4.7uF; 0603-CAP
C2: 1uF; 0603-CAP
D1: NSR0240HT1G; SOD-323
L1: 4.7uH/1.4A; 1007
LED1, LED2, LED3, LED4, LED5, LED6, LED7, LED8, LED9: LEDKA-3528ASYC; KA-3528ASYC
R1: 3.4; R0603
R2: 10k; R0603
U1: OPENMV3
U2: TPS61169; SOT65P210X110-5N
U$4, U$8: FIDUCIAL""; FIDUCIAL_1MM

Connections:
GND: C1.2, C2.2, R1.1, R2.1, U1.28 (GND), U2.GND
LED+: C2.1, D1.1 (C), LED1.A
LED-: LED9.C, R1.2, U2.FB
unnamed: LED1.C, LED2.A
unnamed: LED2.C, LED3.A
unnamed: LED3.C, LED4.A
unnamed: LED4.C, LED5.A
unnamed: LED5.C, LED6.A
unnamed: LED6.C, LED7.A
unnamed: LED7.C, LED8.A
unnamed: LED8.C, LED9.A
PWM: R2.2, U1.17 (ADC/DAC), U2.CTRL
SW: D1.2 (A), L1.2, U2.SW
VIN: C1.1, L1.1, U1.27 (VIN), U2.VIN

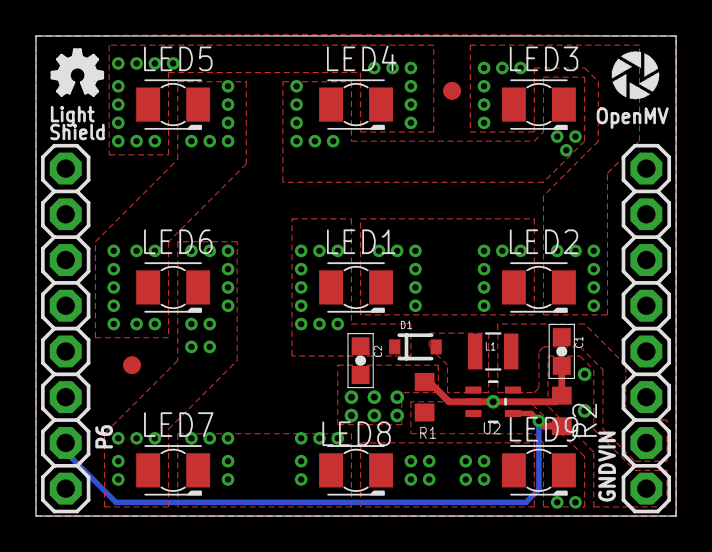
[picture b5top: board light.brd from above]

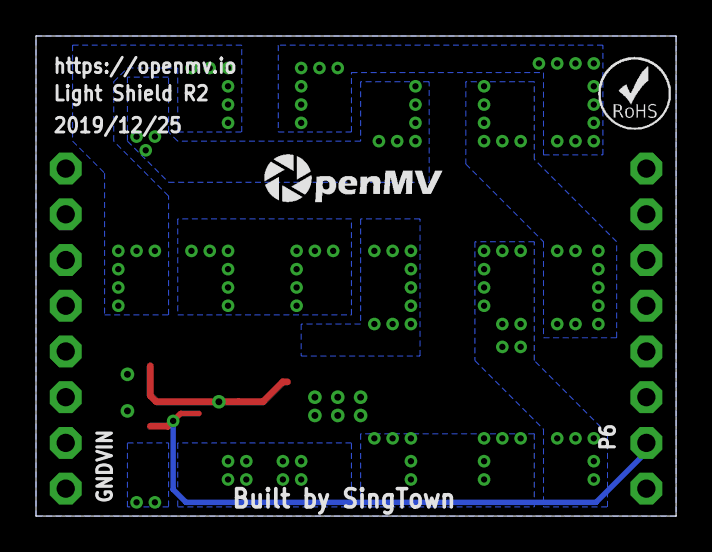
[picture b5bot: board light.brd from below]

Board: 2 copper layers, 35.6 x 26.7 mm, 23 parts (2 on the bottom side), 14 nets.

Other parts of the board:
U$3: ROHS
U$9: OPENMV-LOGO
U$10: OMV-LOGO-SMALL
U$11: OSHW_FILLX100_NOTEXT

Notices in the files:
KiCad_Project/2022/Library/openmv-boards-master/openmv4/sensors/OV2640/OV2640.sch:
Copyright (c) 2018 OpenMV
This work is licensed under the Creative Commons Attribution-ShareAlike 3.0 License.
To view a copy of this license, visit http://creativecommons.org/licenses/by-sa/3.0
KiCad_Project/2022/Library/openmv-boards-master/shields/can/can.sch:
Copyright (c) 2019 OpenMV LLC
This work is licensed under the Creative Commons Attribution-ShareAlike 4.0 License.
To view a copy of this license, visit http://creativecommons.org/licenses/by-sa/4.0
